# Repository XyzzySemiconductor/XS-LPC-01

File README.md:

# Tiny Tapeout Project: Liquid Pump Controller

A digital control chip to daily pump a tank empty. Approached as system design  for a whole product, of which the chip is the core but not only design work required.

- [chip datasheet](docs/LPC_Datasheet.pdf)
- [documentation for Tiny Tapeout chip](docs/info.md)
- [documentation for Tiny Tapeout tests](test/README.md)
- [documentation for MAX10 development fpga](max10/fpga.md)
- [documentation for forge production fpga](forge/forge.md)
- [documentation for the Dev board PCB](pcb/pcb.md)

Branches:
- main - TT design forefront, and Max 10M25 fpga accel of full system sims with hdmi display.
- lpc_emu - Max 10M04 fpga HW emulating the full TT chip (hdmi monitoring)
- lpc_test - Max 10M04 system emulator, chip testing or emulator testing.
- lpc_mon - Max 10M04 chip monitor, passive observation (hdmi)
  
## What is Tiny Tapeout?

Tiny Tapeout is an educational project that aims to make it easier and cheaper than ever to get your digital and analog designs manufactured on a real chip.

To learn more and get started, visit https://tinytapeout.com.

## Set up your Verilog project

1. Add your Verilog files to the `src` folder.
2. Edit the [info.yaml](info.yaml) and update information about your project, paying special attention to the `source_files` and `top_module` properties. If you are upgrading an existing Tiny Tapeout project, check out our [online info.yaml migration tool](https://tinytapeout.github.io/tt-yaml-upgrade-tool/).
3. Edit [docs/info.md](docs/info.md) and add a description of your project.
4. Adapt the testbench to your design. See [test/README.md](test/README.md) for more information.

The GitHub action will automatically build the ASIC files using [LibreLane](https://www.zerotoasiccourse.com/terminology/librelane/).

## Enable GitHub actions to build the results page

- [Enabling GitHub Pages](https://tinytapeout.com/faq/#my-github-action-is-failing-on-the-pages-part)

## Resources

- [FAQ](https://tinytapeout.com/faq/)
- [Digital design lessons](https://tinytapeout.com/digital_design/)
- [Learn how semiconductors work](https://tinytapeout.com/siliwiz/)
- [Join the community](https://tinytapeout.com/discord)
- [Build your design locally](https://www.tinytapeout.com/guides/local-hardening/)

## What next?

- [Submit your design to the next shuttle](https://app.tinytapeout.com/).
- Edit [this README](README.md) and explain your design, how it works, and how to test it.
- Share your project on your social network of choice:
  - LinkedIn [#tinytapeout](https://www.linkedin.com/search/results/content/?keywords=%23tinytapeout) [@TinyTapeout](https://www.linkedin.com/company/100708654/)
  - Mastodon [#tinytapeout](https://chaos.social/tags/tinytapeout) [@matthewvenn](https://chaos.social/@matthewvenn)
  - X (formerly Twitter) [#tinytapeout](https://twitter.com/hashtag/tinytapeout) [@tinytapeout](https://twitter.com/tinytapeout)
  - Bluesky [@tinytapeout.com](https://bsky.app/profile/tinytapeout.com)

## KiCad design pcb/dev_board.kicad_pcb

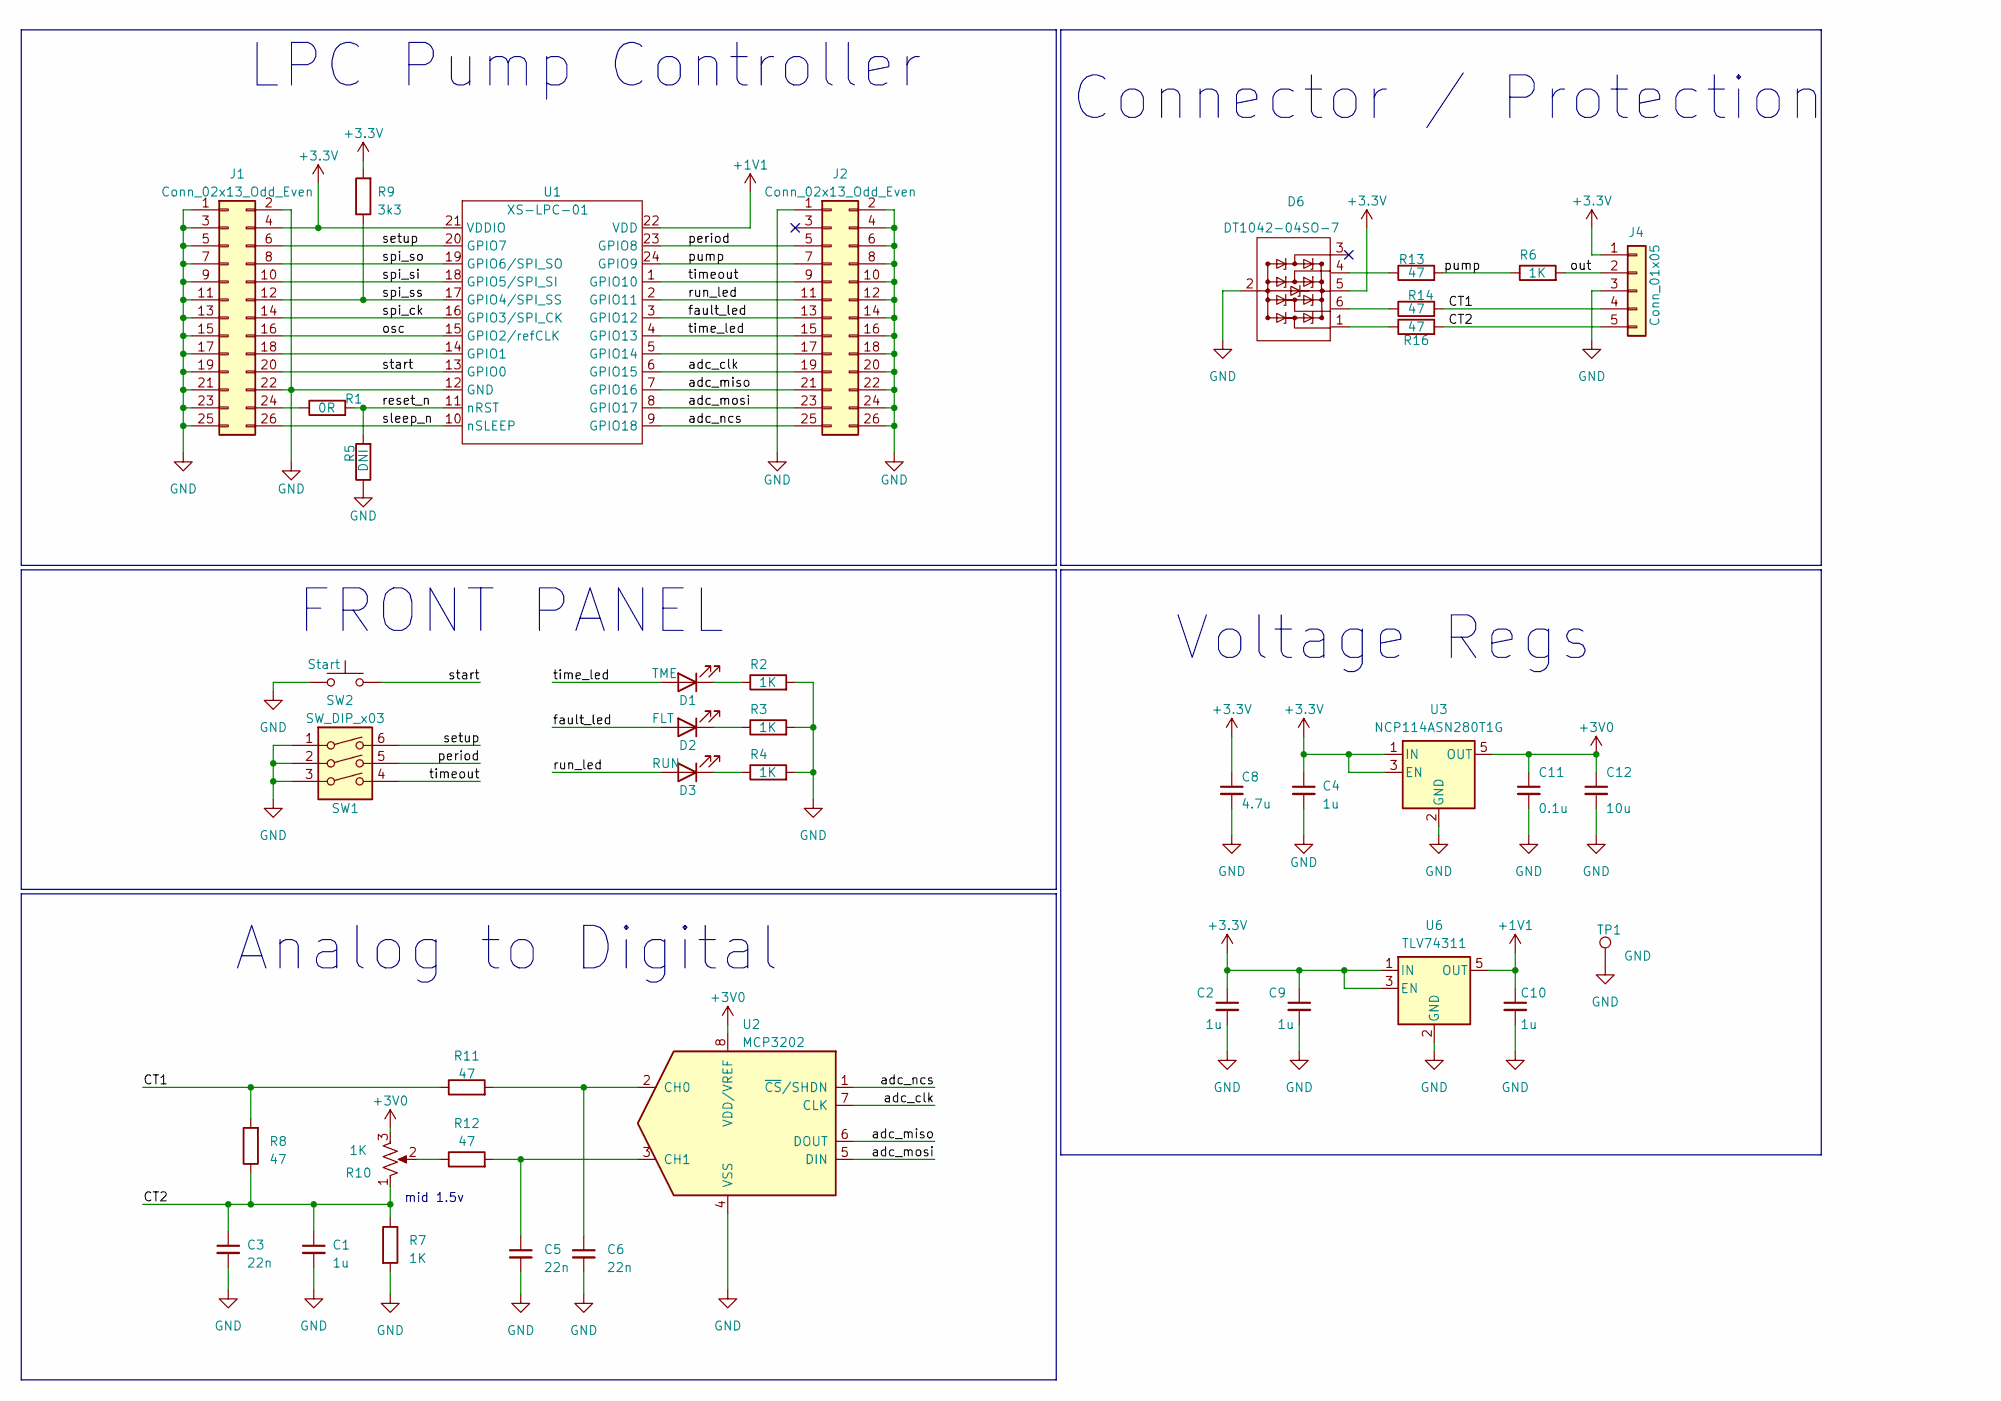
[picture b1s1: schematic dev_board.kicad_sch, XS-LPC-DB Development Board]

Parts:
C1, C2, C4, C9, C10: 1u; C_0603_1608Metric
C3, C5, C6: 22n; C_0603_1608Metric
C8: 4.7u; C_1206_3216Metric
C11: 0.1u; C_0603_1608Metric
C12: 10u; C_1206_3216Metric
D1: TME; LED_0603_1608Metric
D2: FLT; LED_0603_1608Metric
D3: RUN; LED_0603_1608Metric
D6: DT1042-04SO-7; SOT-23-6
J1, J2: Conn_02x13_Odd_Even; PinSocket_2x13_P2.54mm_Vertical
J4: Conn_01x05; CONN_B5B-ZR-SM4-TF_JST
R1: 0R; R_0603_1608Metric; JLC C491211
R2, R3, R4, R6, R7: 1K; R_0603_1608Metric; JLC C319967
R5: DNI; R_0603_1608Metric; JLC C491211
R8, R11, R12, R13, R14, R16: 47; R_0603_1608Metric; JLC C319967
R9: 3k3; R_0603_1608Metric; JLC C319967
R10: 1K; Potentiometer_Bourns_3224J_Horizontal
SW1: SW_DIP_x03; SW_DIP_SPSTx03_Slide_6.7x9.18mm_W6.73mm_P2.54mm_LowProfile_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
SW2: Start; SW_SPST_HP03
TP1: GND; TestPoint_Keystone_5000-5004_Miniature
U1: XS-LPC-01; QFN-24-3x3mm
U2: MCP3202; MSOP-8_3x3mm_P0.65mm
U3: NCP114ASN280T1G; SOT-23-5
U6: TLV74311; SOT-23-5

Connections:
+1V1: C10.1, U1.22 (VDD), U6.5 (OUT)
+3.3V: C2.1, C4.1, C8.1, C9.1, D6.5 (vdd), J1.4, J4.1, R9.2, U1.21 (VDDIO), U3.1 (IN), U3.3 (EN), U6.1 (IN), U6.3 (EN)
+3V0: C11.1, C12.1, R10.3, U2.8 (VDD/VREF), U3.5 (OUT)
/CT1: J4.4, R8.2, R11.1, R14.2
/CT2: C1.1, C3.1, J4.5, R7.1, R8.1, R10.1, R16.2
/adc_clk: J2.19, U1.6 (GPIO15), U2.7 (CLK)
/adc_miso: J2.21, U1.7 (GPIO16), U2.6 (DOUT)
/adc_mosi: J2.23, U1.8 (GPIO17), U2.5 (DIN)
/adc_ncs: J2.25, U1.9 (GPIO18), U2.1 (~CS/SHDN)
/fault_led: D2.2 (A), J2.13, U1.3 (GPIO12)
/osc: J1.16, U1.15 (GPIO2/refCLK)
/out: J4.2, R6.2
/period: J2.5, SW1.5, U1.23 (GPIO8)
/pump: J2.7, R6.1, R13.2, U1.24 (GPIO9)
/reset_n: R1.2, R5.2, U1.11 (nRST)
/run_led: D3.2 (A), J2.11, U1.2 (GPIO11)
/setup: J1.6, SW1.6, U1.20 (GPIO7)
/sleep_n: J1.26, U1.10 (nSLEEP)
/spi_ck: J1.14, U1.16 (GPIO3/SPI_CK)
/spi_si: J1.10, U1.18 (GPIO5/SPI_SI)
/spi_so: J1.8, U1.19 (GPIO6/SPI_SO)
/spi_ss: J1.12, R9.1, U1.17 (GPIO4/SPI_SS)
/start: J1.20, SW2.2, U1.13 (GPIO0)
/time_led: D1.2 (A), J2.15, U1.4 (GPIO13)
/timeout: J2.9, SW1.4, U1.1 (GPIO10)
GND: C1.2, C2.2, C3.2, C4.2, C5.2, C6.2, C8.2, C9.2, C10.2, C11.2, C12.2, D6.2 (vss), J1.1, J1.2, J1.3, J1.5, J1.7, J1.9, J1.11, J1.13, J1.15, J1.17, J1.19, J1.21, J1.22, J1.23, J1.25, J2.1, J2.2, J2.4, J2.6, J2.8, J2.10, J2.12, J2.14, J2.16, J2.18, J2.20, J2.22, J2.24, J2.26, J4.3, R2.2, R3.2, R4.2, R5.1, R7.2, SW1.1, SW1.2, SW1.3, SW2.1, TP1.1, U1.12 (GND), U2.4 (VSS), U3.2 (GND), U6.2 (GND)
unnamed: D1.1 (K), R2.1
unnamed: D2.1 (K), R3.1
unnamed: D3.1 (K), R4.1
unnamed: D6.4 (K1), R13.1
unnamed: D6.6 (K2), R14.1
unnamed: D6.1 (X1), R16.1
unnamed: J1.18, U1.14 (GPIO1)
unnamed: J1.24, R1.1
unnamed: J2.17, U1.5 (GPIO14)
unnamed: R10.2, R12.1
unnamed: C6.1, R11.2, U2.2 (CH0)
unnamed: C5.1, R12.2, U2.3 (CH1)

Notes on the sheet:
LPC Pump Controller
Voltage Regs
FRONT PANEL
Connector / Protection
Analog to Digital
mid 1.5v

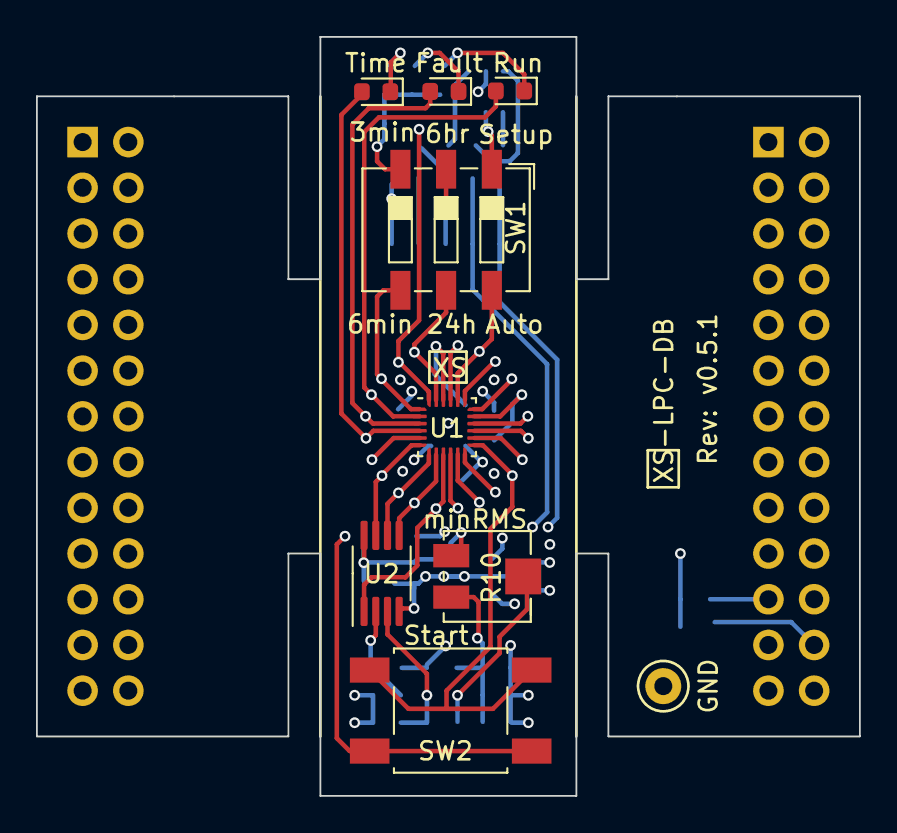
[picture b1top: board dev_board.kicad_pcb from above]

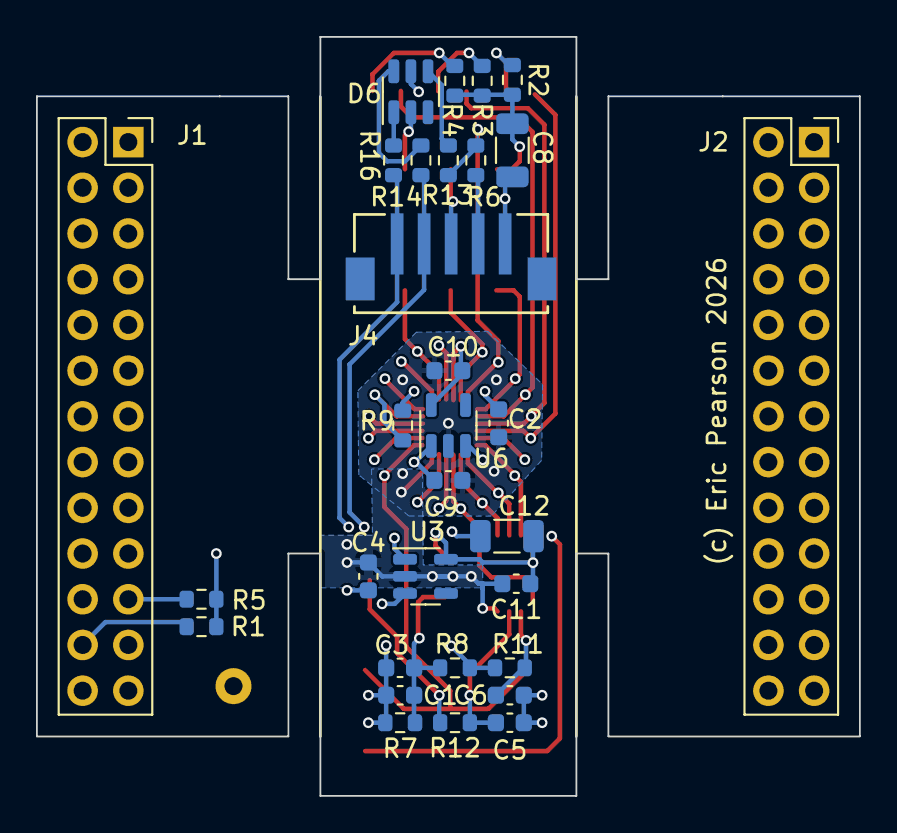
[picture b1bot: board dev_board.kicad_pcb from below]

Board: 6 copper layers, 45.7 x 42.2 mm, 40 parts (31 on the bottom side), 38 nets.

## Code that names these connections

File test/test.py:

# SPDX-FileCopyrightText: © 2024 Tiny Tapeout
# SPDX-License-Identifier: Apache-2.0

import cocotb
from cocotb.clock import Clock
from cocotb.triggers import ClockCycles


@cocotb.test()
async def test_project(dut):
    dut._log.info("Start")

    # Set the clock period to 48 MHz
    clock = Clock(dut.clk, 20832, unit="ps")
    cocotb.start_soon(clock.start())

    # Reset
    dut._log.info("Reset")
    dut.ena.value = 1
    dut.ui_in.value = 0
    dut.uio_in.value = 0
    dut.rst_n.value = 0
    await ClockCycles(dut.clk, 10)
    dut.rst_n.value = 1

    try:
        _ = dut.user_project.i_core.rms_hold_ct.value
        GL_MODE = False
        dut._log.info("RTL Sim")
    except AttributeError:
        GL_MODE = True
        dut._log.info("Gate Sim")

    dut._log.info("Test project behavior")

    # Set the input values you want to test
    # dut.ui_in.value = 20
    # dut.uio_in.value = 30

    # Wait for one clock cycle to see the output values
    assert dut.uio_out.value == (3750>>4)
    if not GL_MODE:
        assert int(dut.user_project.i_core.rms_hold_ct.value) == 0
        assert int(dut.user_project.i_core.rms_hold_ct.value) == 0
    dut._log.info("60 Hz cycle")
    if GL_MODE:
        await ClockCycles(dut.clk, 50000 * 16 + 3200 * 10 )
    if not GL_MODE:
        await ClockCycles(dut.clk, 50000 * 16 * 16)
    #check that flags are OK (and not X)
    assert dut.pump_out.value  == 1
    #assert dut.time_led.value  == 1
    assert dut.run_led.value   == 1
    # check RMS values
    if GL_MODE:
        assert dut.fault_led.value == 1
    if not GL_MODE:
        assert dut.fault_led.value == 0
        assert int(dut.user_project.i_core.rms_hold_ct.value) < (1200*1200*3750)
        assert int(dut.user_project.i_core.rms_hold_ct.value) > (1000*1000*3750)
        assert int(dut.user_project.i_core.rms_hold_ct.value) == 4154053977
        assert int(dut.user_project.i_core.rms_hold_ref.value) < (600*600*3750)
        assert int(dut.user_project.i_core.rms_hold_ref.value) > (500*500*3750)
        #assert int(dut.user_project.i_core.rms_hold_ref.value) == 1038448055

    # The following assersion is just an example of how to check the output values.
    # Change it to match the actual expected output of your module:
    #assert dut.uo_out.value == 50

    # Keep testing the module by changing the input values, waiting for
    # one or more clock cycles, and asserting the expected output values.

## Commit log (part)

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2026-06-19 get new chip starting structure roughed out
